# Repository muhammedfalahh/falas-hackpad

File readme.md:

# Falas Hackpad

This is my custom Hackpad built for the Hackpad challenge.  
The idea was to keep it simple, clean, and fully custom from schematic to PCB to case.

Everything here is open and easy to understand so anyone can learn from it or build their own version.

---

## Overall Hackpad

This shows the full hackpad and how the PCB fits inside the case.

---

## Schematic

The complete schematic used for this hackpad, including the microcontroller and switch connections.

---

## PCB Layout

The PCB layout showing switch placement, routing, and overall board design.

---

## Case and Fit

This shows the case design and how all parts fit together.

---

## Bill of Materials BOM

| Part | Quantity | Notes |
|-----|----------|------|
| Microcontroller | 1 | XIAO RP2040 or compatible |
| Mechanical Switches | 4 | MX style |
| Diodes | 4 | For switch inputs |
| Custom PCB | 1 | Designed in KiCad |
| Case | 1 | 3D printed |
| USB Cable | 1 | Power and programming |

---

## Firmware

The firmware is written in CircuitPython.  
It handles key input and basic macro functionality.

You can find the firmware files inside the firmware folder.

---

## Project Structure

- PCB contains the KiCad schematic and PCB files  
- CAD contains the case design files  
- Firmware contains the CircuitPython code  
- images contains all screenshots used in this README  

---

## Notes

This project was created for the Hackpad challenge and follows open source principles.  
Feel free to fork it, improve it, or build your own version from it.

Thanks for checking it out.

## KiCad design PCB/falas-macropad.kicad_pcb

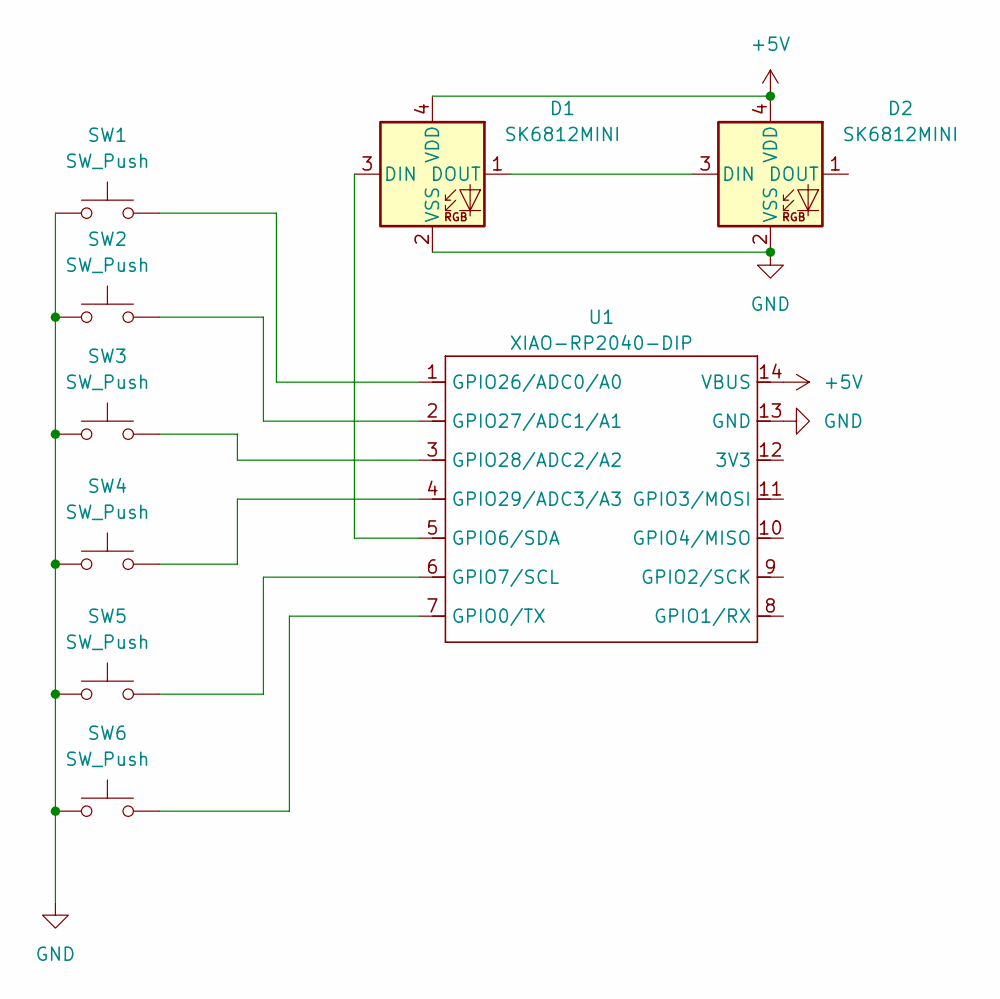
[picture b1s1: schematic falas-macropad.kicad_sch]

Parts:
D1, D2: SK6812MINI; LED_SK6812MINI_PLCC4_3.5x3.5mm_P1.75mm
SW1, SW2, SW3, SW4, SW5, SW6: SW_Push; SW_Cherry_MX_1.00u_PCB
U1: XIAO-RP2040-DIP

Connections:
+5V: D1.4 (VDD), D2.4 (VDD), U1.14 (VBUS)
GND: D1.2 (VSS), D2.2 (VSS), SW1.1, SW2.1, SW3.1, SW4.1, SW5.1, SW6.1, U1.13 (GND)
unnamed: D1.3 (DIN), U1.5 (GPIO6/SDA)
unnamed: D1.1 (DOUT), D2.3 (DIN)
unnamed: SW6.2, U1.7 (GPIO0/TX)
unnamed: SW5.2, U1.6 (GPIO7/SCL)
unnamed: SW1.2, U1.1 (GPIO26/ADC0/A0)
unnamed: SW2.2, U1.2 (GPIO27/ADC1/A1)
unnamed: SW3.2, U1.3 (GPIO28/ADC2/A2)
unnamed: SW4.2, U1.4 (GPIO29/ADC3/A3)

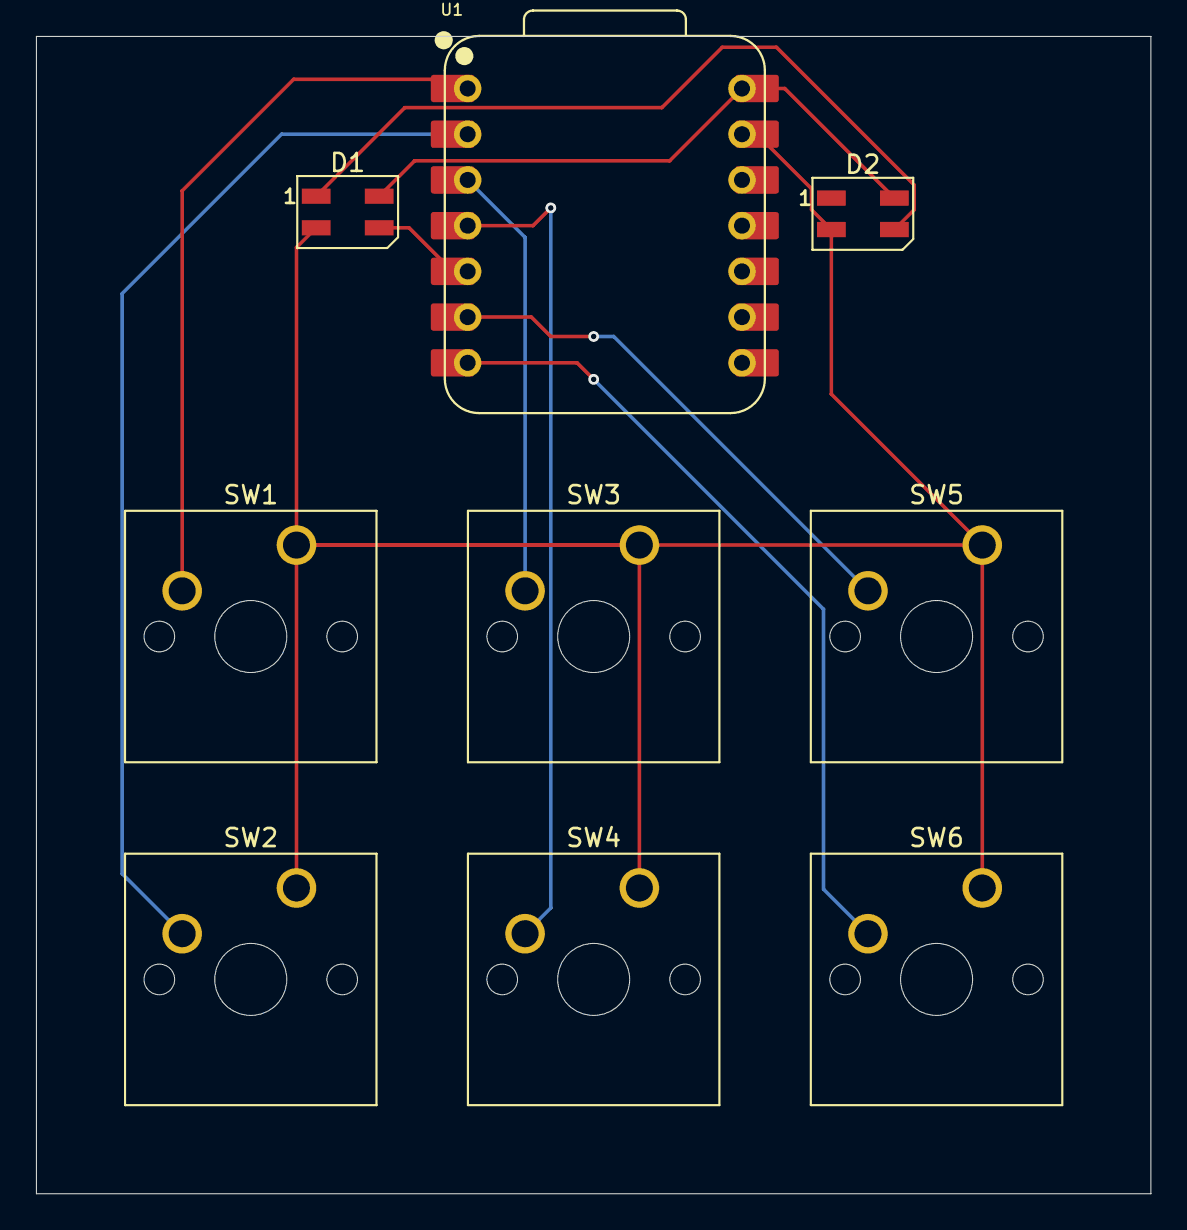
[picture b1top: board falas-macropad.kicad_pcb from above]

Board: 2 copper layers, 61.9 x 64.3 mm, 9 parts (0 on the bottom side), 10 nets.

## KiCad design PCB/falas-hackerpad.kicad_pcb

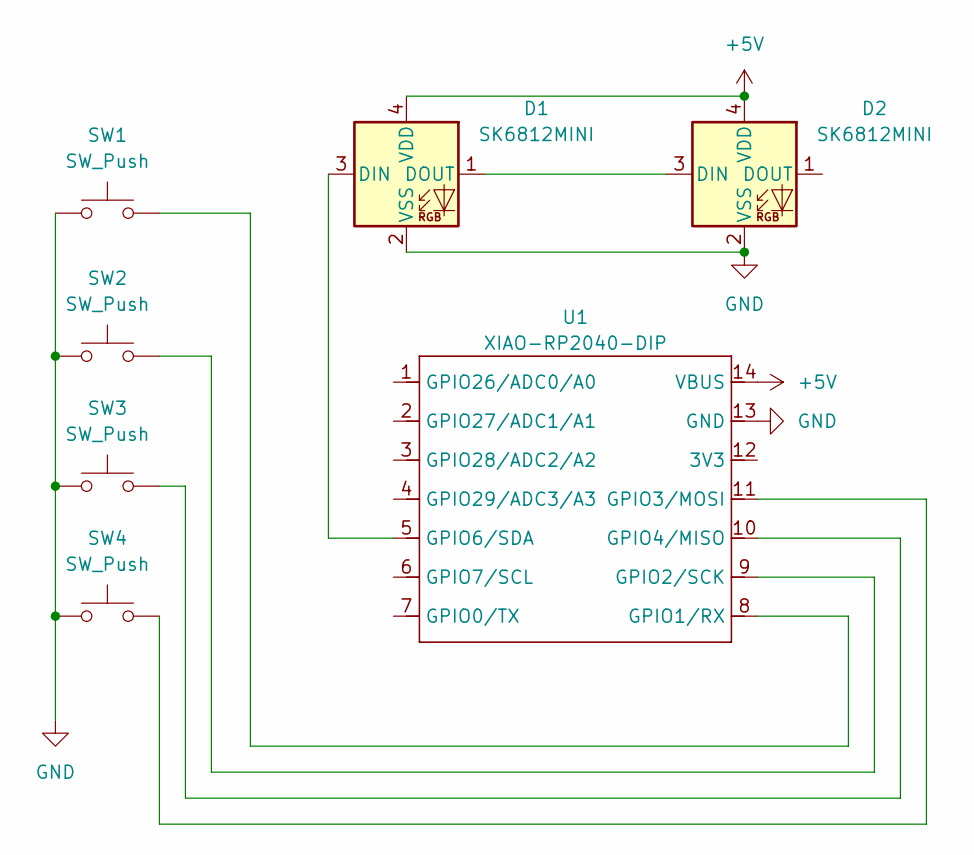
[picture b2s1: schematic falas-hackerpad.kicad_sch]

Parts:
D1, D2: SK6812MINI; LED_SK6812MINI_PLCC4_3.5x3.5mm_P1.75mm
SW1, SW2, SW3, SW4: SW_Push; SW_Cherry_MX_1.00u_PCB
U1: XIAO-RP2040-DIP

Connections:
+5V: D1.4 (VDD), D2.4 (VDD), U1.14 (VBUS)
GND: D1.2 (VSS), D2.2 (VSS), SW1.1, SW2.1, SW3.1, SW4.1, U1.13 (GND)
unnamed: D1.3 (DIN), U1.5 (GPIO6/SDA)
unnamed: D1.1 (DOUT), D2.3 (DIN)
unnamed: SW1.2, U1.8 (GPIO1/RX)
unnamed: SW2.2, U1.9 (GPIO2/SCK)
unnamed: SW4.2, U1.11 (GPIO3/MOSI)
unnamed: SW3.2, U1.10 (GPIO4/MISO)

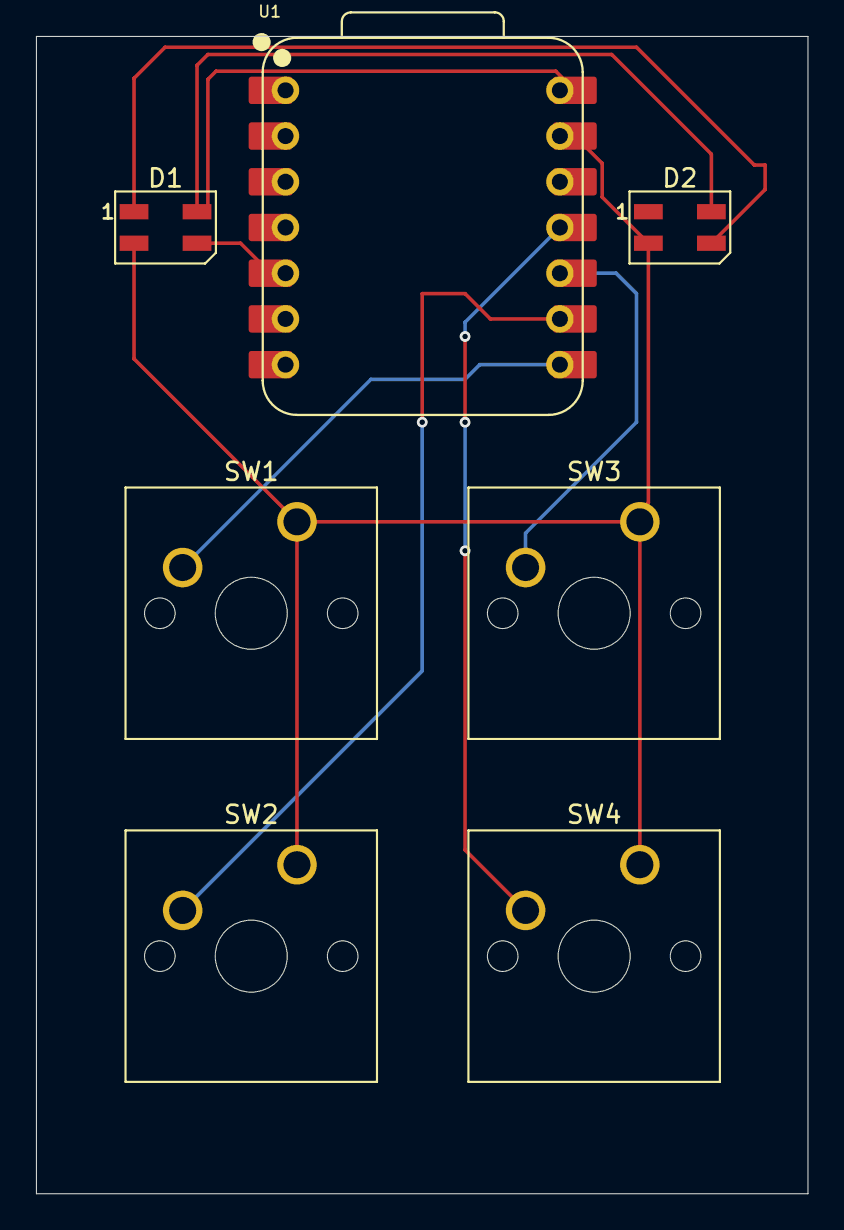
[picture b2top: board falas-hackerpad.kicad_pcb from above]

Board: 2 copper layers, 42.9 x 64.3 mm, 7 parts (0 on the bottom side), 8 nets.

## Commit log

2025-12-25 removed-unneccesary-files
2025-12-25 some-improvements-to-the-documentations
